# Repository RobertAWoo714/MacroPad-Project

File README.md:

# MacroPad-Project

A small Macropad with 13 mx cherry switches, 2 rotary encoders with tactile buttons, and 13 holes for sk6812 RGBs.

Repo contains:

1. Schematic/PCB files made in Kicad 

2. Firmware .ino made in Arduino IDE

3. 3D CAD made in SOLIDWORKS

Solidworks Final CAD:

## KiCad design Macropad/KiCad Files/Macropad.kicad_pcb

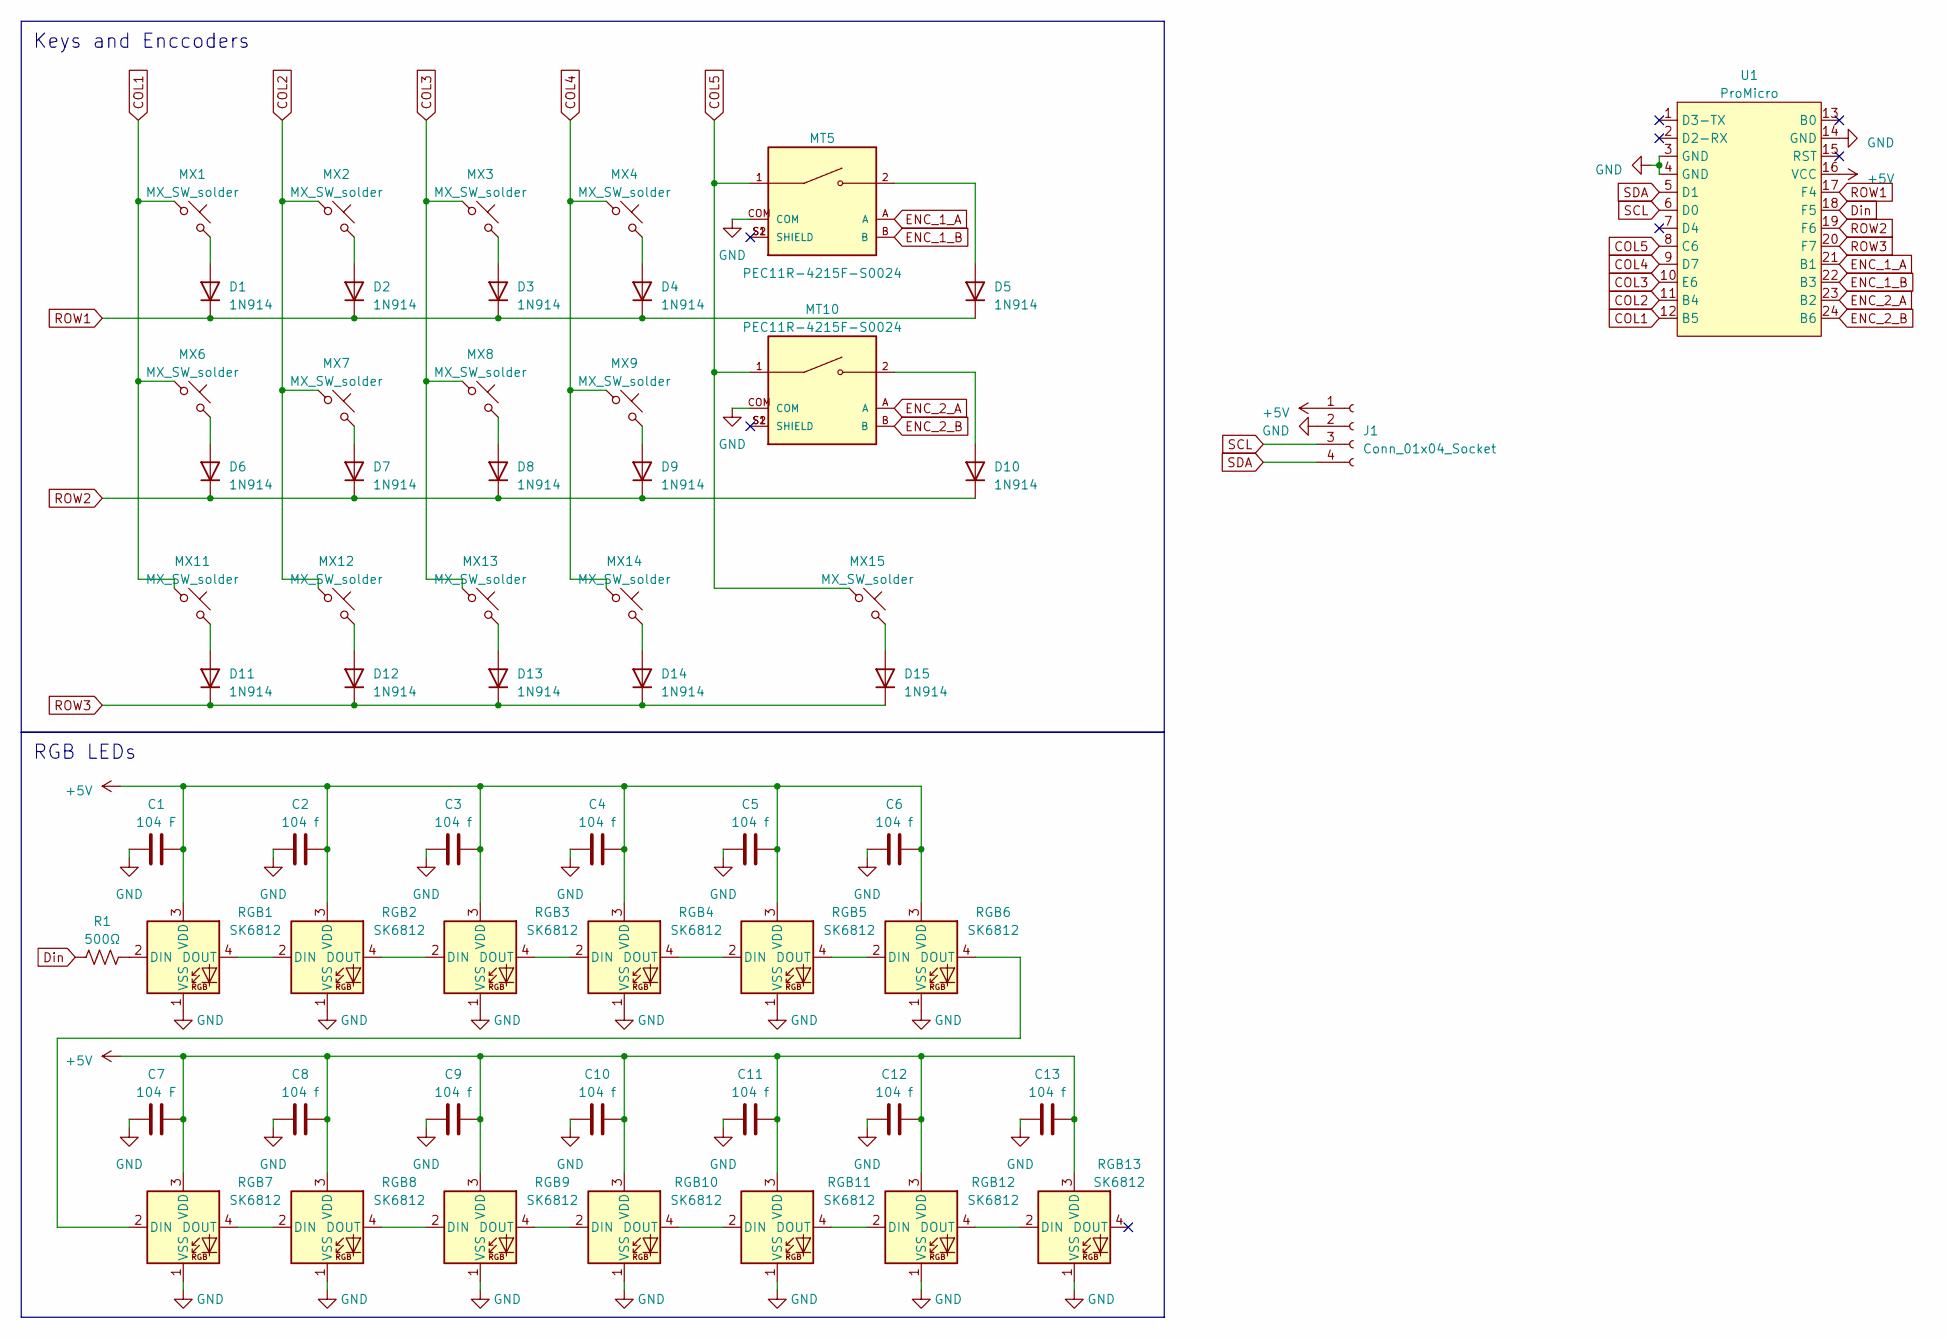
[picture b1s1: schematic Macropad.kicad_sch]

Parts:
C1, C7: 104 F; C_0402_1005Metric
C2, C3, C4, C5, C6, C8, C9, C10, C11, C12, C13: 104 f; C_0402_1005Metric
D1, D2, D3, D4, D5, D6, D7, D8, D9, D10, D11, D12, D13, D14, D15: 1N914; D_SOD-123
J1: Conn_01x04_Socket; PinHeader_1x04_P2.00mm_Vertical
MT5, MT10: PEC11R-4215F-S0024; XDCR_PEC11R-4215F-S0024; PARTREV Rev. 09/19
MX1, MX2, MX3, MX4, MX6, MX7, MX8, MX9, MX11, MX12, MX13, MX14, MX15: MX_SW_solder; SW_MX_1u
R1: 500Ω; R_Axial_DIN0207_L6.3mm_D2.5mm_P10.16mm_Horizontal
RGB1, RGB2, RGB3, RGB4, RGB5, RGB6, RGB7, RGB8, RGB9, RGB10, RGB11, RGB12, RGB13: SK6812; SK6812 mini-e
U1: ProMicro; ProMicro_USBup

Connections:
+5V: C1.2, C2.2, C3.2, C4.2, C5.2, C6.2, C7.2, C8.2, C9.2, C10.2, C11.2, C12.2, C13.2, J1.1, RGB1.3 (VDD), RGB2.3 (VDD), RGB3.3 (VDD), RGB4.3 (VDD), RGB5.3 (VDD), RGB6.3 (VDD), RGB7.3 (VDD), RGB8.3 (VDD), RGB9.3 (VDD), RGB10.3 (VDD), RGB11.3 (VDD), RGB12.3 (VDD), RGB13.3 (VDD), U1.16 (VCC)
COL1: MX1.1, MX6.1, MX11.1, U1.12 (B5)
COL2: MX2.1, MX7.1, MX12.1, U1.11 (B4)
COL3: MX3.1, MX8.1, MX13.1, U1.10 (E6)
COL4: MX4.1, MX9.1, MX14.1, U1.9 (D7)
COL5: MT5.1, MT10.1, MX15.1, U1.8 (C6)
Din: R1.1, U1.18 (F5)
ENC_1_A: MT5.A, U1.21 (B1)
ENC_1_B: MT5.B, U1.22 (B3)
ENC_2_A: MT10.A, U1.23 (B2)
ENC_2_B: MT10.B, U1.24 (B6)
GND: C1.1, C2.1, C3.1, C4.1, C5.1, C6.1, C7.1, C8.1, C9.1, C10.1, C11.1, C12.1, C13.1, J1.2, MT5.COM, MT10.COM, RGB1.1 (VSS), RGB2.1 (VSS), RGB3.1 (VSS), RGB4.1 (VSS), RGB5.1 (VSS), RGB6.1 (VSS), RGB7.1 (VSS), RGB8.1 (VSS), RGB9.1 (VSS), RGB10.1 (VSS), RGB11.1 (VSS), RGB12.1 (VSS), RGB13.1 (VSS), U1.3 (GND), U1.4 (GND), U1.14 (GND)
unnamed: D1.2 (A), MX1.2
unnamed: D2.2 (A), MX2.2
unnamed: D3.2 (A), MX3.2
unnamed: D4.2 (A), MX4.2
unnamed: D5.2 (A), MT5.2
unnamed: D6.2 (A), MX6.2
unnamed: D7.2 (A), MX7.2
unnamed: D8.2 (A), MX8.2
unnamed: D9.2 (A), MX9.2
unnamed: D10.2 (A), MT10.2
unnamed: D11.2 (A), MX11.2
unnamed: D12.2 (A), MX12.2
unnamed: D13.2 (A), MX13.2
unnamed: D14.2 (A), MX14.2
unnamed: D15.2 (A), MX15.2
unnamed: R1.2, RGB1.2 (DIN)
unnamed: RGB1.4 (DOUT), RGB2.2 (DIN)
unnamed: RGB2.4 (DOUT), RGB3.2 (DIN)
unnamed: RGB3.4 (DOUT), RGB4.2 (DIN)
unnamed: RGB4.4 (DOUT), RGB5.2 (DIN)
unnamed: RGB5.4 (DOUT), RGB6.2 (DIN)
unnamed: RGB6.4 (DOUT), RGB7.2 (DIN)
unnamed: RGB7.4 (DOUT), RGB8.2 (DIN)
unnamed: RGB8.4 (DOUT), RGB9.2 (DIN)
unnamed: RGB9.4 (DOUT), RGB10.2 (DIN)
unnamed: RGB10.4 (DOUT), RGB11.2 (DIN)
unnamed: RGB11.4 (DOUT), RGB12.2 (DIN)
unnamed: RGB12.4 (DOUT), RGB13.2 (DIN)
ROW1: D1.1 (K), D2.1 (K), D3.1 (K), D4.1 (K), D5.1 (K), U1.17 (F4)
ROW2: D6.1 (K), D7.1 (K), D8.1 (K), D9.1 (K), D10.1 (K), U1.19 (F6)
ROW3: D11.1 (K), D12.1 (K), D13.1 (K), D14.1 (K), D15.1 (K), U1.20 (F7)
SCL: J1.3, U1.6 (D0)
SDA: J1.4, U1.5 (D1)

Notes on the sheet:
Keys and Enccoders
RGB LEDs

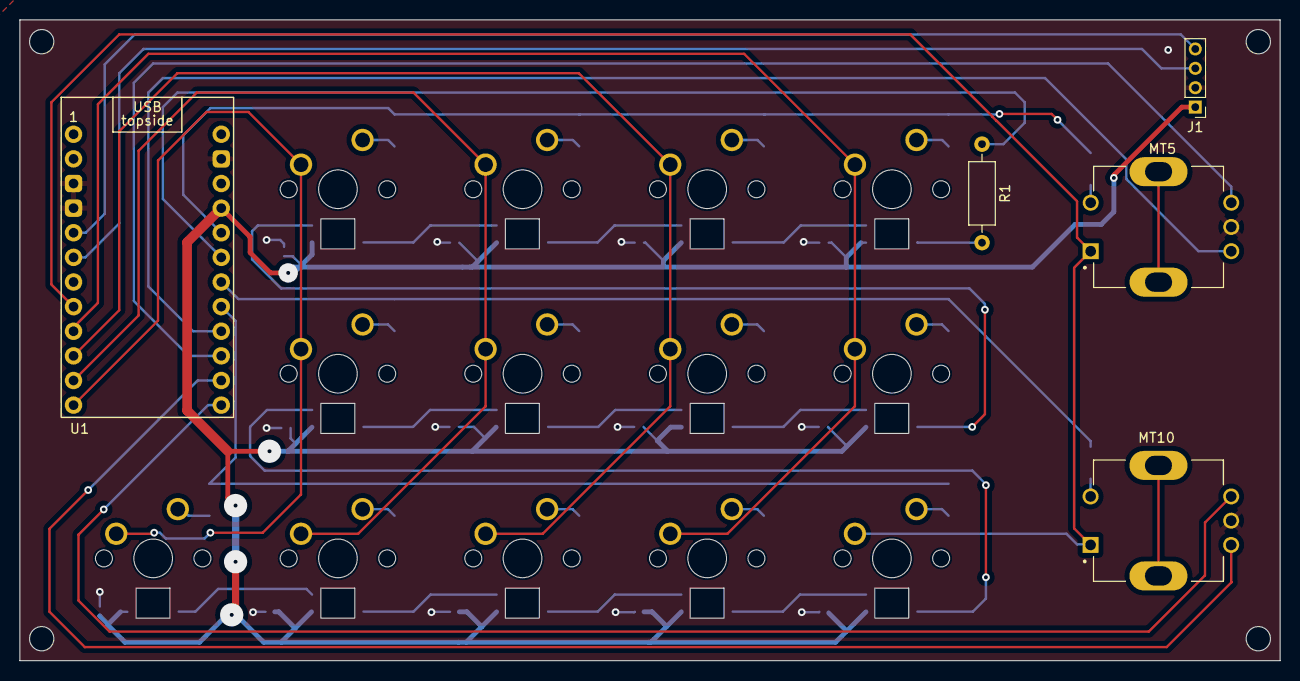
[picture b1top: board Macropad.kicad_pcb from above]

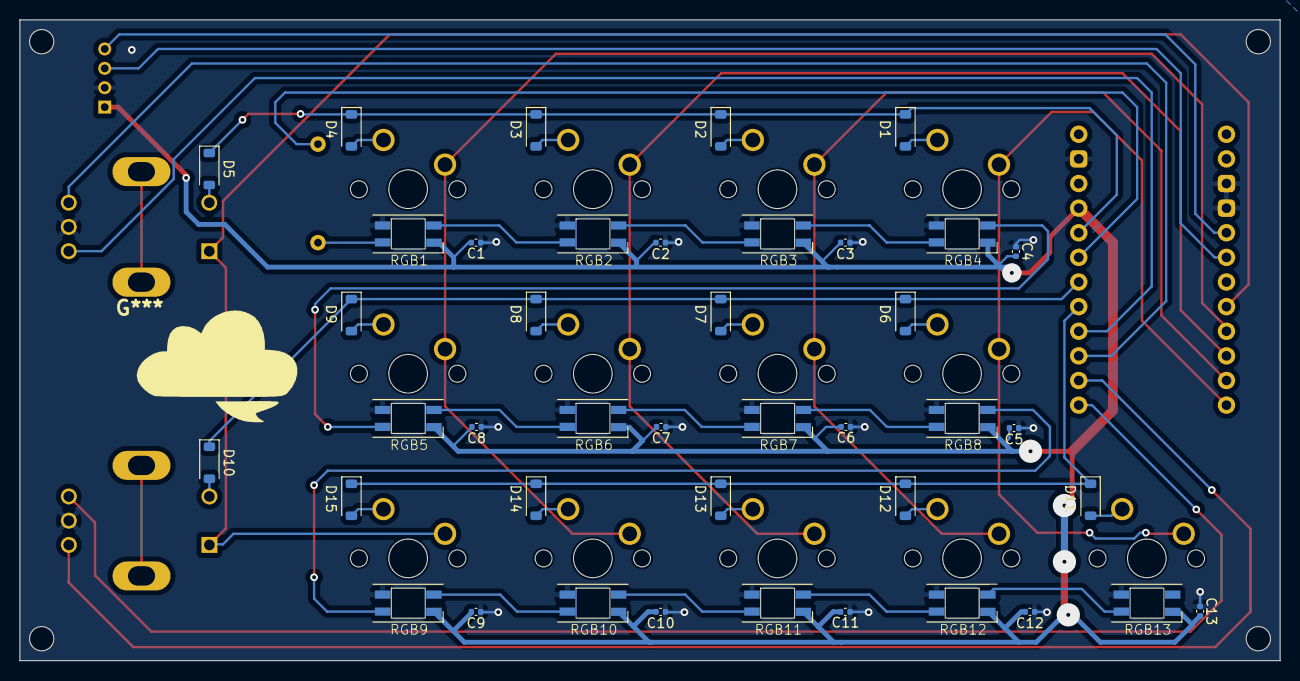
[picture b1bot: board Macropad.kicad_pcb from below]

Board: 2 copper layers, 130.0 x 66.1 mm, 59 parts (41 on the bottom side), 45 nets.
